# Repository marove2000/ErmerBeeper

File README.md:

# Ermer Beeper

The Ermer Beeper is a very neat continuity tester or beeper. This one is VERY fast and also faster than the most multimeters. No display, no LED, no switch. Just a speaker to beep you through your circuit. Based on a gread scientist [Christof Ermer](https://homepages.uni-regensburg.de/~erc24492/)

- Status: **Complete**
- Difficulty: **2/5**

### Parts List

| Quantity | Name   | Description           | Signing/Colorcode             |
|----------|--------|-----------------------|-------------------------------|
| 2        | C1, C2 | 100nF capacitor       | 104                           |
| 1        | R1     | 1k Ohm resistor 1%    | brown-black-black-brown-brown |
| 2        | R2, R3 | 5,6k Ohm resistor 1%  | green-blue-black-brown-brown  |
| 1        | R4     | 56 Ohm resistor 1%    | green-blue-black-gold-brown   |
| 2        | Q1, Q2 | BC547C NPN transistor | BC547                         |
| 1        | LS1    | 50 Ohm speaker        |                               |
| 2        | J1, J2 | 4mm binding posts     |                               |
| 1        | BAT1   | 2xAA battery holder   |                               |
| 2        |        | 2xAA batteries*       |                               |
| 7        |        | wooden box parts**    |                               |
| 1        |        | PCB                   |                               |

* The batteries are not included in our kits.
** The wooden parts are optional.

### Additional Add-Ons
If you need test leads you can use any you already have. I've found these on Aliexpress: https://www.aliexpress.com/item/4000119525148.html

### Manual
You can find the manual and pictures of every step here: https://github.com/Binary-Kitchen/SolderingTutorial

### Copyright and Authorship

- Board: [CC-BY-SA 4.0](https://creativecommons.org/licenses/by-sa/4.0/) - Timo Schindler @ [blinkyparts.com](https://shop.blinkyparts.com)
- Outline SVG [CC-0](https://de.wikipedia.org/wiki/Gemeinfreiheit) - [Wikipedia: Datei:Delta-shield.svg](https://de.wikipedia.org/wiki/Datei:Delta-shield.svg)
- Idea and scheme: [Christoph Ermer](https://homepages.uni-regensburg.de/~erc24492/)

### Buy Soldering Kits
If you want to buy the parts and PCB for a soldering kit you can find everything here: [shop.blinkyparts.com](https://shop.blinkyparts.com/de/Ermer-Piepser-Durchgangspruefer-nicht-von-dieser-Welt/blink233942)

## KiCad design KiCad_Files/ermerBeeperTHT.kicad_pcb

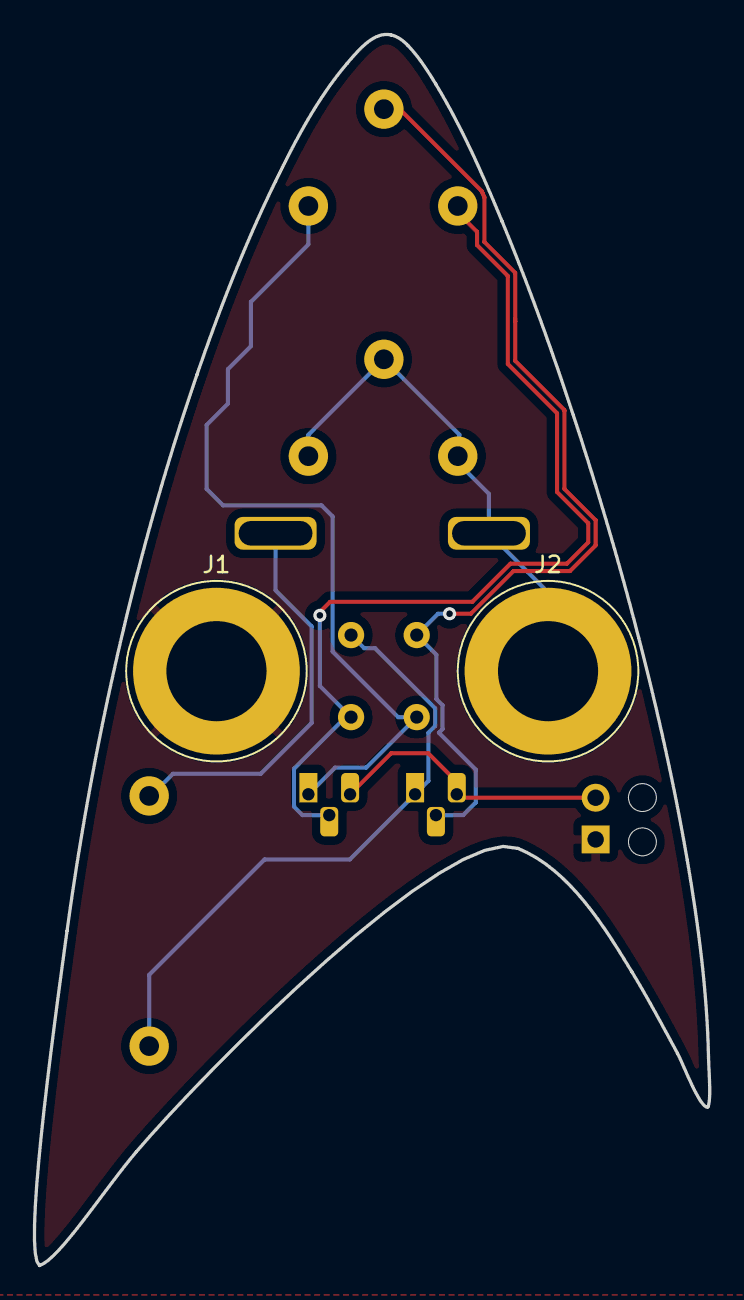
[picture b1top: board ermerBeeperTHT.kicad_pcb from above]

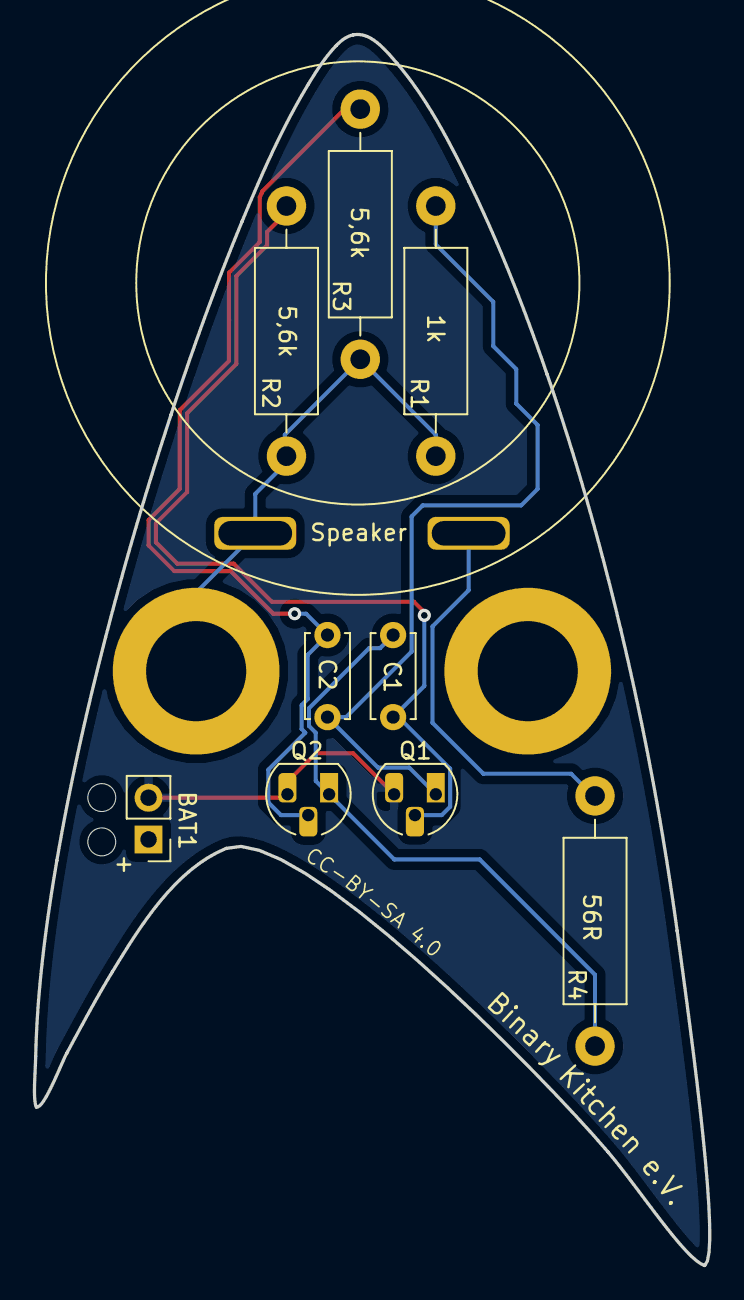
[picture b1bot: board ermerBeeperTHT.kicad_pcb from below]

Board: 2 copper layers, 41.1 x 75.0 mm, 12 parts (10 on the bottom side), 8 nets.

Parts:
BAT1: Battery_Cell; PinHeader_1x02_P2.54mm_Vertical
C1, C2: 100nF; C_Disc_D5.0mm_W2.5mm_P5.00mm
J1, J2: Conn_01x01_Female; Banana_Jack_1Pin
LS1: Speaker
Q1, Q2: Q_NPN_CBE; TO-92L_HandSolder
R1: 1k; R_Axial_DIN0411_L9.9mm_D3.6mm_P15.24mm_Horizontal
R2, R3: 5,6k; R_Axial_DIN0411_L9.9mm_D3.6mm_P15.24mm_Horizontal
R4: 56R; R_Axial_DIN0411_L9.9mm_D3.6mm_P15.24mm_Horizontal

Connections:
+3V0: BAT1.1, J1.1
GND: BAT1.2, Q1.3, Q2.3
unnamed: C1.1, Q2.1, R4.2
unnamed: C1.2, Q1.2, R2.2
unnamed: C2.1, Q2.2, R3.2
unnamed: C2.2, Q1.1, R1.2
unnamed: J2.1, LS1.1, R1.1, R2.1, R3.1
unnamed: LS1.2, R4.1

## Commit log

2022-09-16 added first gitignore
2022-09-16 added readme and license-file
2022-09-16 fixed bug
2022-09-16 fixed another bug
2022-09-16 enlarged picture
2022-09-16 added box files
2022-09-16 added KiCad-Files
